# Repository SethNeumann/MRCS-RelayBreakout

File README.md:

# MRCS-RelayBreakout
## License: Creative Commons Attribution-NonCommercial-ShareAlike

Breakout for OMRON style DPDT relay

Relays come in handy in many telephone applications.  This is an
inexpensive DPDT (2 form C) relay suitable for controlling 2A loads,
serving as a latch for lights and buzzers, providing a contact
multiplier etc.  The relays come in many voltage options from 3-48
VDC, so the board can be customized for many different applications.

This differs from the inexpensive "Arduino Relays" in that the
inputs are necessarily logic compatible and in that these are DPDT
whereas the "Arduino Relays" are typically only Single Pole Double Throw (SPDT).

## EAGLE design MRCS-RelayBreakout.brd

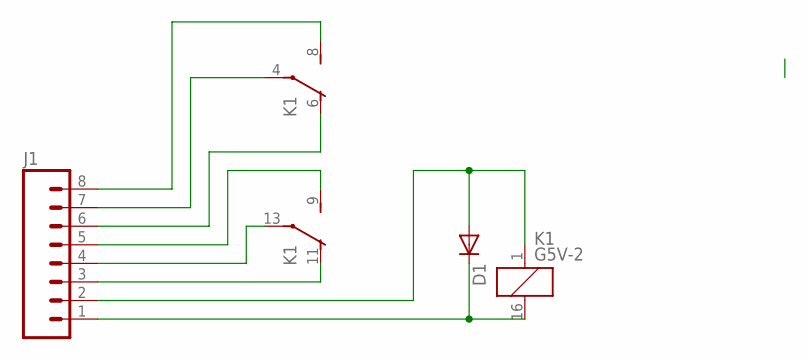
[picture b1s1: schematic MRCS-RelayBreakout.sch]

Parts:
D1: DIODEPTH; DIODE-1N4001
J1: CONNECTOR-M08LOCK; 1X08_LOCK
K1: G5V-2

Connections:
unnamed: D1.C, J1.1, K1.16 (2)
unnamed: D1.A, J1.2, K1.1
unnamed: J1.3, K1.11 (O)
unnamed: J1.4, K1.13
unnamed: J1.5, K1.9 (S)
unnamed: J1.6, K1.6 (O)
unnamed: J1.7, K1.4
unnamed: J1.8, K1.8 (S)

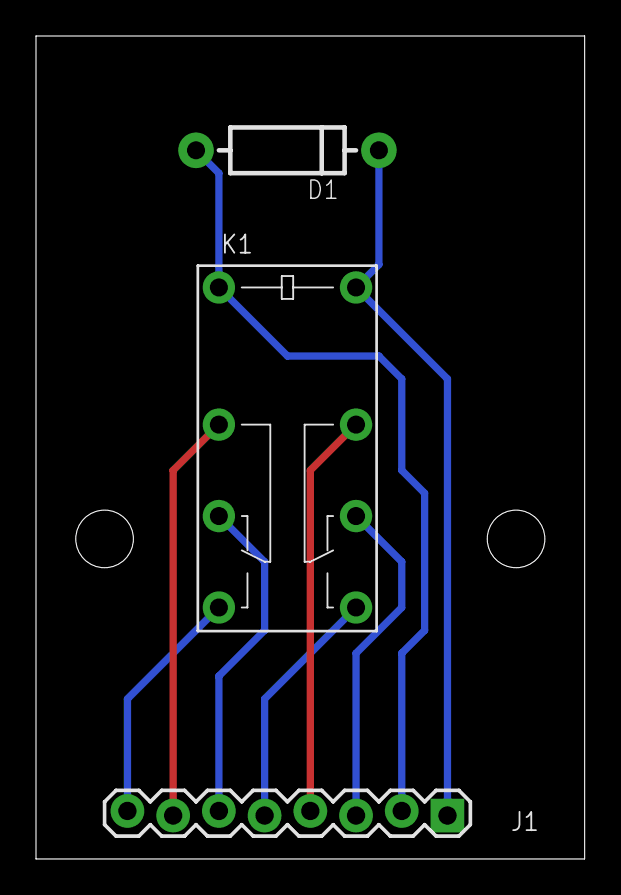
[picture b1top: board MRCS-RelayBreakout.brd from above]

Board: 2 copper layers, 30.5 x 45.7 mm, 4 parts (0 on the bottom side), 8 nets.

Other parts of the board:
U$1: MRCSLOGOTOP

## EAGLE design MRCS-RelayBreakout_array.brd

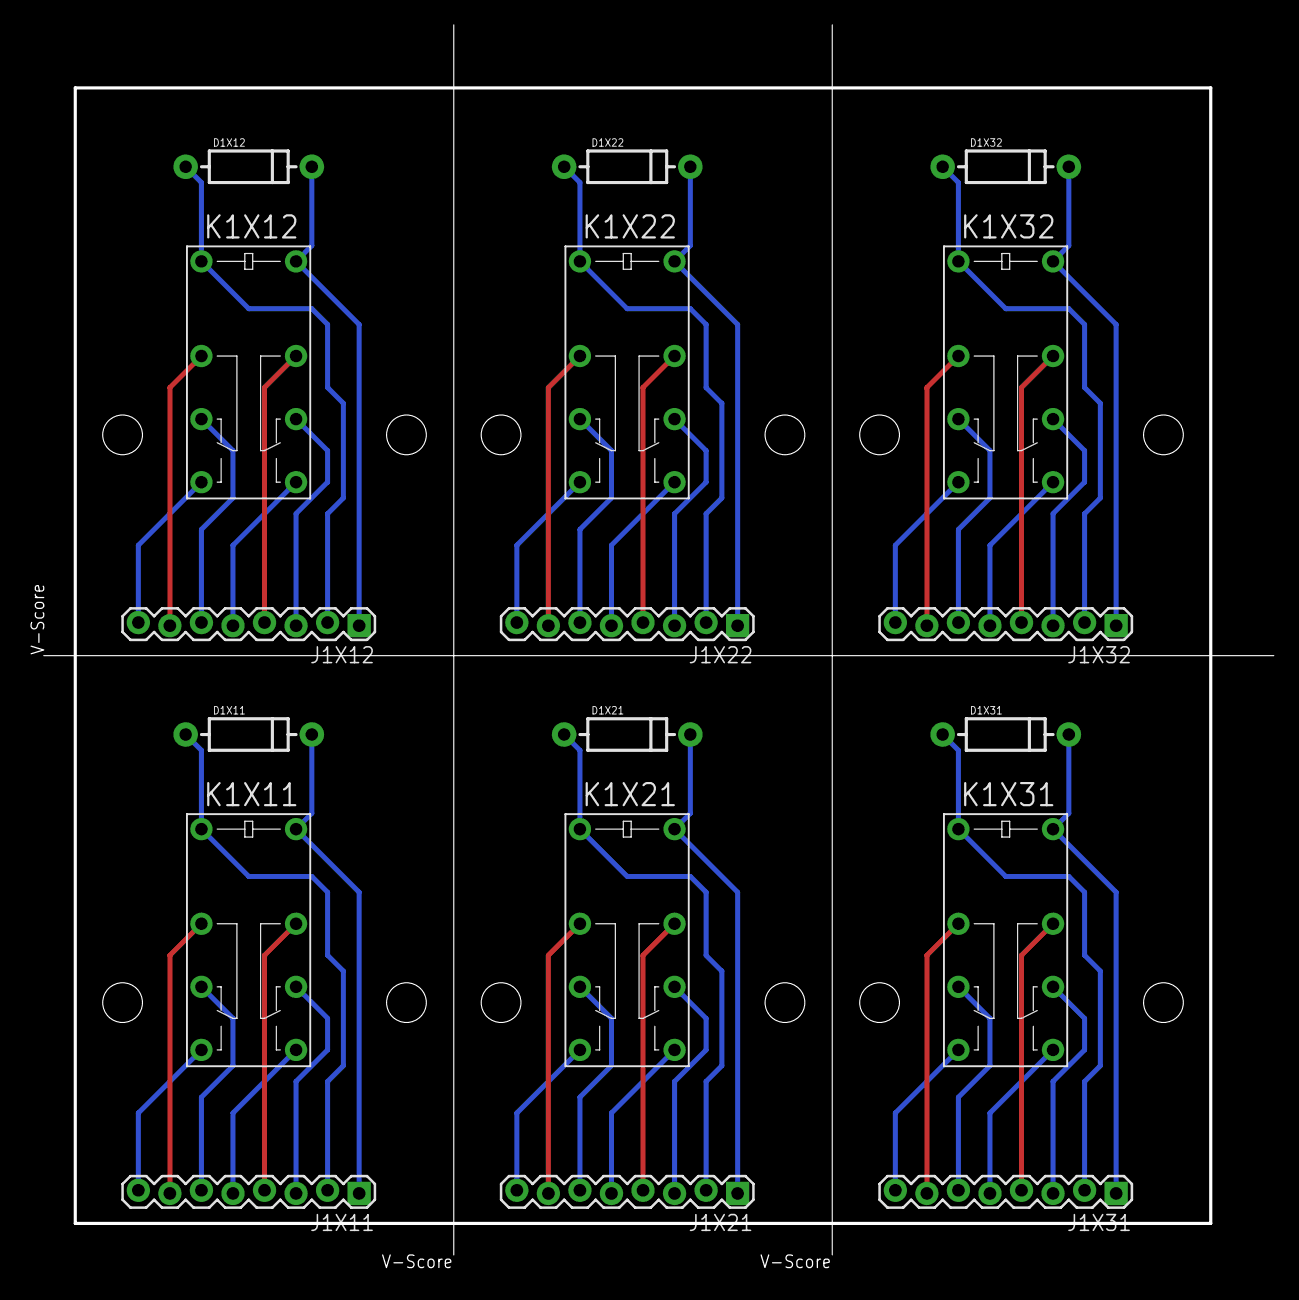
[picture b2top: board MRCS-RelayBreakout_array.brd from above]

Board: 2 copper layers, 100.3 x 100.4 mm, 24 parts (0 on the bottom side), 48 nets.

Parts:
D1X11, D1X12, D1X21, D1X22, D1X31, D1X32: DIODE-1N4001
J1X11, J1X12, J1X21, J1X22, J1X31, J1X32: 1X08_LOCK
K1X11, K1X12, K1X21, K1X22, K1X31, K1X32: G5V-2
U$1X11, U$1X12, U$1X21, U$1X22, U$1X31, U$1X32: MRCSLOGOTOP

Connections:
unnamed: D1X11.C, J1X11.1, K1X11.16
unnamed: D1X12.C, J1X12.1, K1X12.16
unnamed: D1X21.C, J1X21.1, K1X21.16
unnamed: D1X22.C, J1X22.1, K1X22.16
unnamed: D1X31.C, J1X31.1, K1X31.16
unnamed: D1X32.C, J1X32.1, K1X32.16
unnamed: D1X11.A, J1X11.2, K1X11.1
unnamed: D1X12.A, J1X12.2, K1X12.1
unnamed: D1X21.A, J1X21.2, K1X21.1
unnamed: D1X22.A, J1X22.2, K1X22.1
unnamed: D1X31.A, J1X31.2, K1X31.1
unnamed: D1X32.A, J1X32.2, K1X32.1
unnamed: J1X11.3, K1X11.11
unnamed: J1X12.3, K1X12.11
unnamed: J1X21.3, K1X21.11
unnamed: J1X22.3, K1X22.11
unnamed: J1X31.3, K1X31.11
unnamed: J1X32.3, K1X32.11
unnamed: J1X11.4, K1X11.13
unnamed: J1X12.4, K1X12.13
unnamed: J1X21.4, K1X21.13
unnamed: J1X22.4, K1X22.13
unnamed: J1X31.4, K1X31.13
unnamed: J1X32.4, K1X32.13
unnamed: J1X11.5, K1X11.9
unnamed: J1X12.5, K1X12.9
unnamed: J1X21.5, K1X21.9
unnamed: J1X22.5, K1X22.9
unnamed: J1X31.5, K1X31.9
unnamed: J1X32.5, K1X32.9
unnamed: J1X11.6, K1X11.6
unnamed: J1X12.6, K1X12.6
unnamed: J1X21.6, K1X21.6
unnamed: J1X22.6, K1X22.6
unnamed: J1X31.6, K1X31.6
unnamed: J1X32.6, K1X32.6
unnamed: J1X11.7, K1X11.4
unnamed: J1X12.7, K1X12.4
unnamed: J1X21.7, K1X21.4
unnamed: J1X22.7, K1X22.4
unnamed: J1X31.7, K1X31.4
unnamed: J1X32.7, K1X32.4
unnamed: J1X11.8, K1X11.8
unnamed: J1X12.8, K1X12.8
unnamed: J1X21.8, K1X21.8
unnamed: J1X22.8, K1X22.8
unnamed: J1X31.8, K1X31.8
unnamed: J1X32.8, K1X32.8

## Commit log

2019-11-28 ensured License is CC-NC-SA
2019-11-28 Telephone Tag
2020-05-04 updated tags
